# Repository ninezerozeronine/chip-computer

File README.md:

# 16 bit Computer

This is a project to make a basic but fully functional 16 bit computer 
using 7400 series ICs.

The full docs can be found on the Read the Docs: https://eight-bit-computer.readthedocs.io/

# Docs

To build the docs on mac run:

    make clean
    make html

in `docs`.

To build the docs in windows run:

    sphinx-build.exe . _build

in `docs`. This also runs the apidoc command on build with a convenience function in conf.py.

# Tests

To run the tests, run:

    tox

in the root directory. Note that in pytest.ini the tests directory is specified as the test directory.

Run:

    tox -e test -- -m "not slow"

To avoid the slow checks.

To generate a coverage report run:

    tox -e cov

in the root directory.

# Development

This is assuming the OS is Windows and Anaconda is being used for Python/Environment managemnet.

If one hasn't already been created, create a virtualenv with:

    conda create --name chipcomputerenv python=3.11

Then activate the virtualenv:

    conda activate sbcdevenv

Then install the package into the dev env by running the following in the root directory:

    python -m pip install .

# Release

    python setup.py sdist bdist_wheel
    python -m twine upload dist/*

# License

The content of this project itself is licensed under the
[Attribution-ShareAlike 4.0 International
license](http://creativecommons.org/licenses/by-sa/4.0/), and any source code used
in conjunction with the project is licensed under the [MIT
license](http://opensource.org/licenses/mit-license.php).

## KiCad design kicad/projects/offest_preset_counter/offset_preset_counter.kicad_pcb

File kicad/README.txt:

templates
    KiCad templates for boards in the computer
    https://docs.kicad-pcb.org/5.1/en/kicad/kicad.html#project_templates

symbol_libs
    Symbol libraries shared between the KiCad project.
    The templates are set up to point to these.

projects
    A folder to contain the KiCad projects.
    Each board is it's own project.

footprint_libs
    Footprint libraries shared between the KiCad projects.
    The templates are set up to point to these.

Library referncing is achieved via the KiCad variable replacement in the project library settings:
    ${KIPRJMOD}\..\..\symbol_libs\eight-bit-computer.lib
    ${KIPRJMOD}\..\..\footprint_libs\eight-bit-computer.pretty

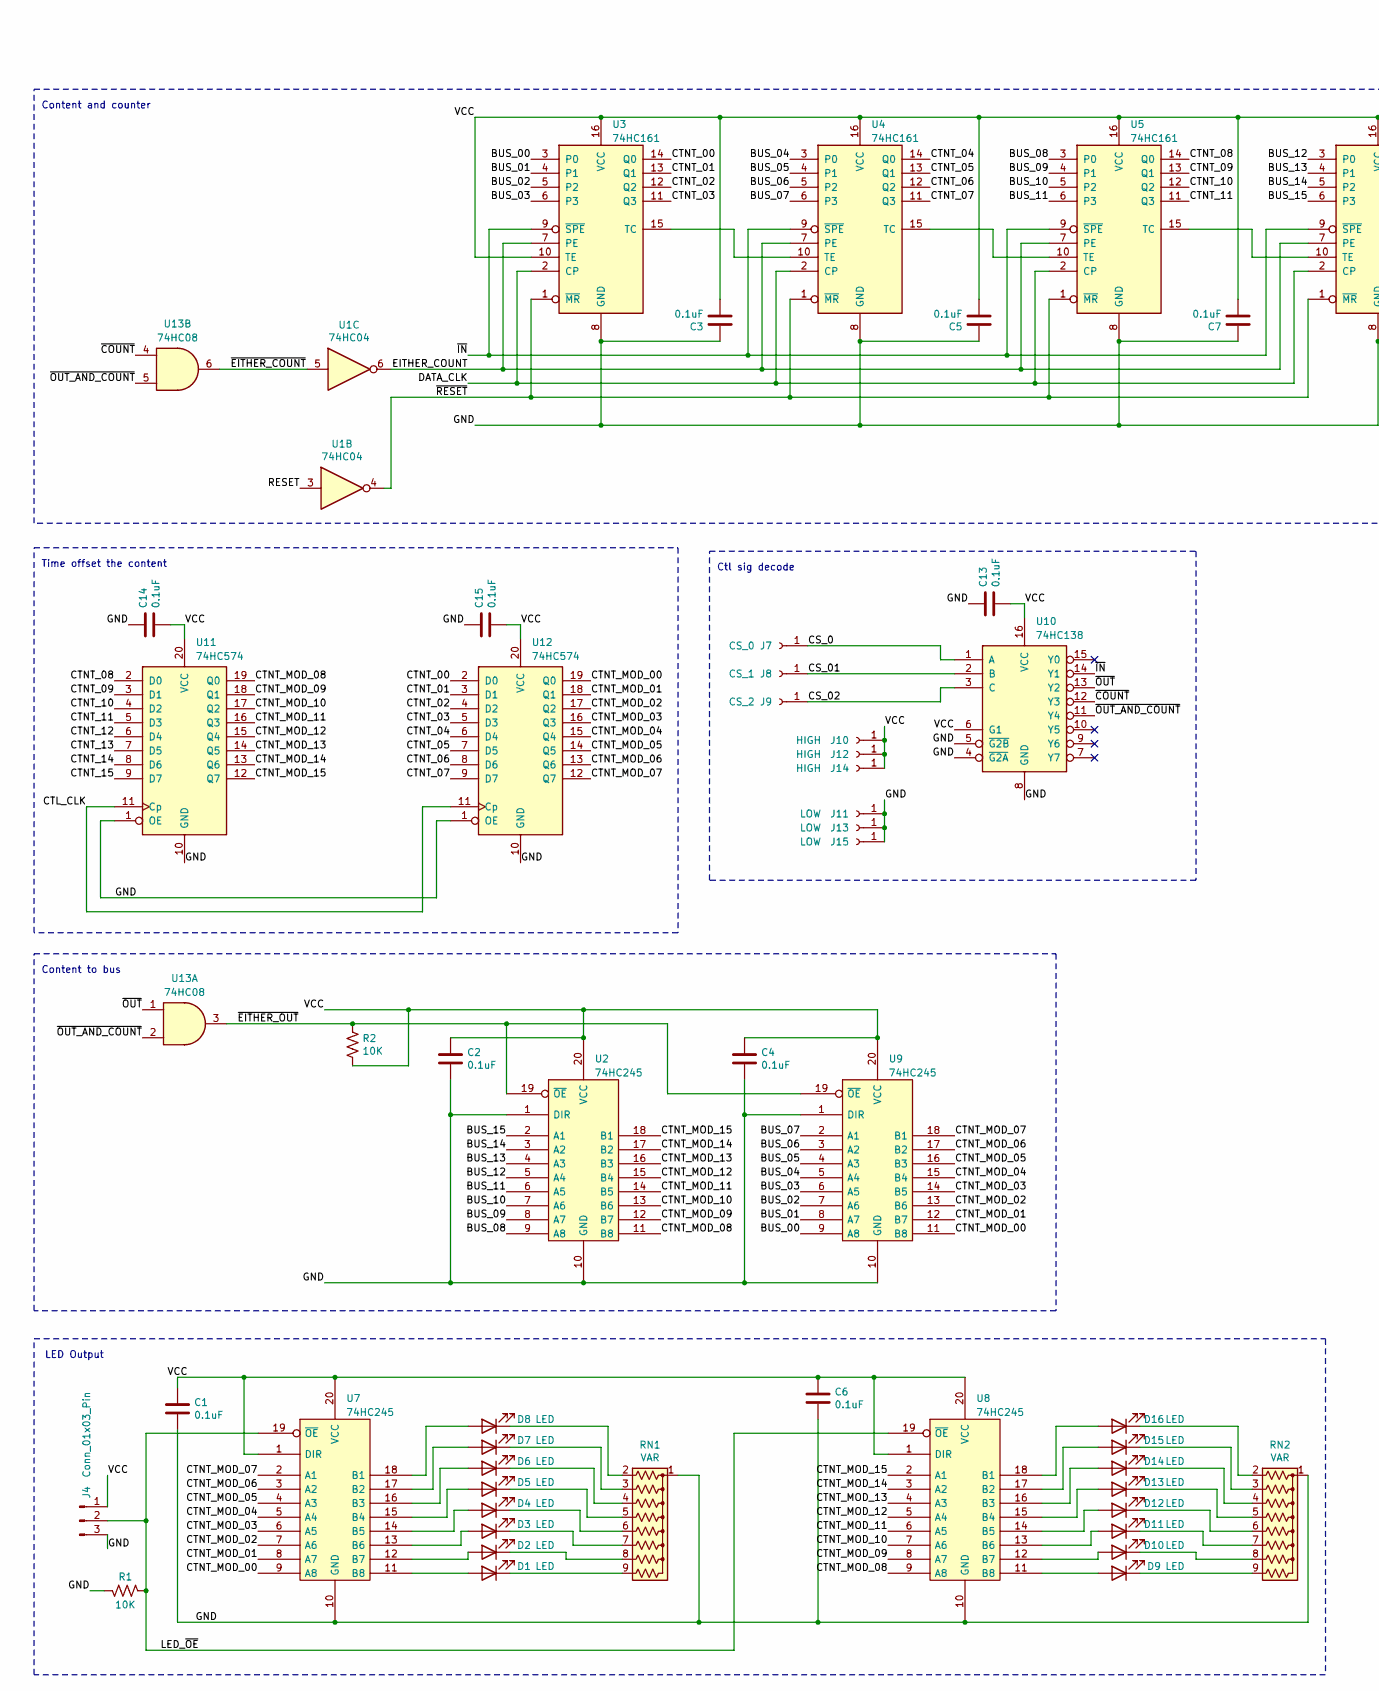
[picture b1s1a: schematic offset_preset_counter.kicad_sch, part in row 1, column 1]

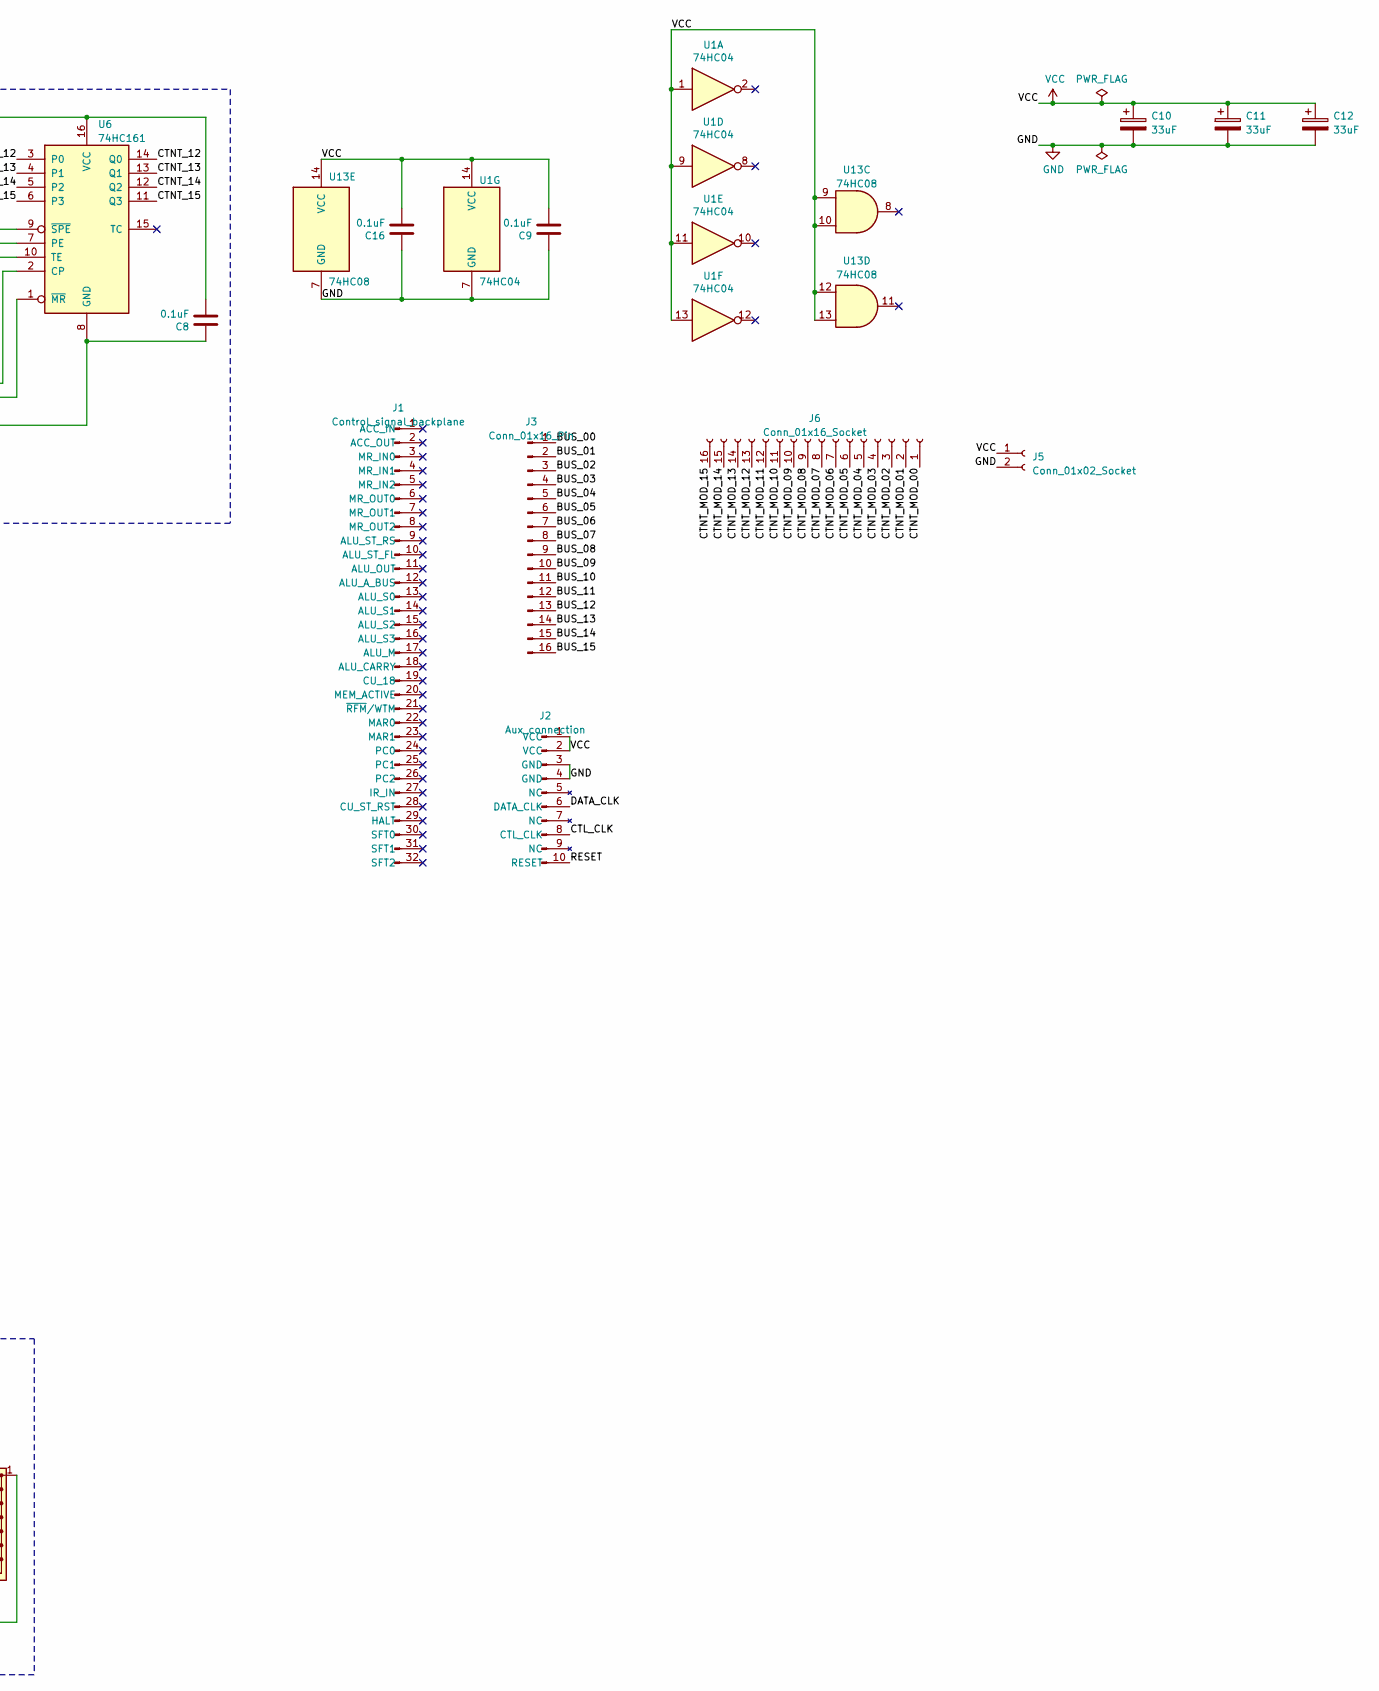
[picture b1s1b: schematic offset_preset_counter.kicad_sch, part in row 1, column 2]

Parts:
C1, C2, C3, C4, C5, C6, C7, C8, C9, C13, C14, C15, C16: 0.1uF; C_Disc_D5.0mm_W2.5mm_P5.00mm
C10, C11, C12: 33uF; CP_Radial_D6.3mm_P2.50mm
D1, D2, D3, D4, D5, D6, D7, D8, D9, D10, D11, D12, D13, D14, D15, D16: LED; LED_D5.0mm_Horizontal_O3.81mm_Z3.0mm
J1: Control_signal_backplane; backplane-connector-annotated
J2: Aux_connection; aux-connection
J3: Conn_01x16_Pin; bus-connection
J4: Conn_01x03_Pin; PinHeader_1x03_P2.54mm_Horizontal
J5: Conn_01x02_Socket; PinSocket_1x02_P2.54mm_Horizontal
J6: Conn_01x16_Socket; PinSocket_1x16_P2.54mm_Horizontal
J7: CS_0; SolderWire-0.5sqmm_1x01_D0.9mm_OD2.3mm
J8: CS_1; SolderWire-0.5sqmm_1x01_D0.9mm_OD2.3mm
J9: CS_2; SolderWire-0.5sqmm_1x01_D0.9mm_OD2.3mm
J10, J12, J14: HIGH; SolderWire-0.5sqmm_1x01_D0.9mm_OD2.3mm
J11, J13, J15: LOW; SolderWire-0.5sqmm_1x01_D0.9mm_OD2.3mm
R1, R2: 10K; R_Axial_DIN0207_L6.3mm_D2.5mm_P10.16mm_Horizontal
RN1, RN2: VAR; R_Array_SIP9
U1: 74HC04; DIP-14_W7.62mm_Socket
U2, U7, U8, U9: 74HC245; DIP-20_W7.62mm_Socket
U3, U4, U5, U6: 74HC161; DIP-16_W7.62mm_Socket
U10: 74HC138; DIP-16_W7.62mm_Socket
U11, U12: 74HC574; DIP-20_W7.62mm_Socket
U13: 74HC08; DIP-14_W7.62mm_Socket

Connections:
/BUS_00: J3.1, U3.3 (P0), U9.9 (A8)
/BUS_01: J3.2, U3.4 (P1), U9.8 (A7)
/BUS_02: J3.3, U3.5 (P2), U9.7 (A6)
/BUS_03: J3.4, U3.6 (P3), U9.6 (A5)
/BUS_04: J3.5, U4.3 (P0), U9.5 (A4)
/BUS_05: J3.6, U4.4 (P1), U9.4 (A3)
/BUS_06: J3.7, U4.5 (P2), U9.3 (A2)
/BUS_07: J3.8, U4.6 (P3), U9.2 (A1)
/BUS_08: J3.9, U2.9 (A8), U5.3 (P0)
/BUS_09: J3.10, U2.8 (A7), U5.4 (P1)
/BUS_10: J3.11, U2.7 (A6), U5.5 (P2)
/BUS_11: J3.12, U2.6 (A5), U5.6 (P3)
/BUS_12: J3.13, U2.5 (A4), U6.3 (P0)
/BUS_13: J3.14, U2.4 (A3), U6.4 (P1)
/BUS_14: J3.15, U2.3 (A2), U6.5 (P2)
/BUS_15: J3.16, U2.2 (A1), U6.6 (P3)
/CS_0: J7.1, U10.1 (A)
/CS_01: J8.1, U10.2 (B)
/CS_02: J9.1, U10.3 (C)
/CTL_CLK: J2.8 (CTL_CLK), U11.11 (Cp), U12.11 (Cp)
/CTNT_00: U3.14 (Q0), U12.2 (D0)
/CTNT_01: U3.13 (Q1), U12.3 (D1)
/CTNT_02: U3.12 (Q2), U12.4 (D2)
/CTNT_03: U3.11 (Q3), U12.5 (D3)
/CTNT_04: U4.14 (Q0), U12.6 (D4)
/CTNT_05: U4.13 (Q1), U12.7 (D5)
/CTNT_06: U4.12 (Q2), U12.8 (D6)
/CTNT_07: U4.11 (Q3), U12.9 (D7)
/CTNT_08: U5.14 (Q0), U11.2 (D0)
/CTNT_09: U5.13 (Q1), U11.3 (D1)
/CTNT_10: U5.12 (Q2), U11.4 (D2)
/CTNT_11: U5.11 (Q3), U11.5 (D3)
/CTNT_12: U6.14 (Q0), U11.6 (D4)
/CTNT_13: U6.13 (Q1), U11.7 (D5)
/CTNT_14: U6.12 (Q2), U11.8 (D6)
/CTNT_15: U6.11 (Q3), U11.9 (D7)
/CTNT_MOD_00: J6.1, U7.9 (A8), U9.11 (B8), U12.19 (Q0)
/CTNT_MOD_01: J6.2, U7.8 (A7), U9.12 (B7), U12.18 (Q1)
/CTNT_MOD_02: J6.3, U7.7 (A6), U9.13 (B6), U12.17 (Q2)
/CTNT_MOD_03: J6.4, U7.6 (A5), U9.14 (B5), U12.16 (Q3)
/CTNT_MOD_04: J6.5, U7.5 (A4), U9.15 (B4), U12.15 (Q4)
/CTNT_MOD_05: J6.6, U7.4 (A3), U9.16 (B3), U12.14 (Q5)
/CTNT_MOD_06: J6.7, U7.3 (A2), U9.17 (B2), U12.13 (Q6)
/CTNT_MOD_07: J6.8, U7.2 (A1), U9.18 (B1), U12.12 (Q7)
/CTNT_MOD_08: J6.9, U2.11 (B8), U8.9 (A8), U11.19 (Q0)
/CTNT_MOD_09: J6.10, U2.12 (B7), U8.8 (A7), U11.18 (Q1)
/CTNT_MOD_10: J6.11, U2.13 (B6), U8.7 (A6), U11.17 (Q2)
/CTNT_MOD_11: J6.12, U2.14 (B5), U8.6 (A5), U11.16 (Q3)
/CTNT_MOD_12: J6.13, U2.15 (B4), U8.5 (A4), U11.15 (Q4)
/CTNT_MOD_13: J6.14, U2.16 (B3), U8.4 (A3), U11.14 (Q5)
/CTNT_MOD_14: J6.15, U2.17 (B2), U8.3 (A2), U11.13 (Q6)
/CTNT_MOD_15: J6.16, U2.18 (B1), U8.2 (A1), U11.12 (Q7)
/DATA_CLK: J2.6 (DATA_CLK), U3.2 (CP), U4.2 (CP), U5.2 (CP), U6.2 (CP)
/EITHER_COUNT: U1.6, U3.7 (PE), U4.7 (PE), U5.7 (PE), U6.7 (PE)
/LED_~OE: J4.2, R1.1, U7.19 (~OE), U8.19 (~OE)
/RESET: J2.10 (RESET), U1.3
/~COUNT: U10.12 (Y3), U13.4
/~EITHER_COUNT: U1.5, U13.6
/~EITHER_OUT: R2.1, U2.19 (~OE), U9.19 (~OE), U13.3
/~IN: U3.9 (~SPE), U4.9 (~SPE), U5.9 (~SPE), U6.9 (~SPE), U10.14 (Y1)
/~OUT_AND_COUNT: U10.11 (Y4), U13.2, U13.5
/~OUT: U10.13 (Y2), U13.1
/~RESET: U1.4, U3.1 (~MR), U4.1 (~MR), U5.1 (~MR), U6.1 (~MR)
GND: C1.2, C2.2, C3.1, C4.2, C5.1, C6.2, C7.1, C8.1, C9.1, C10.2, C11.2, C12.2, C13.1, C14.1, C15.1, C16.1, J2.3 (GND), J2.4 (GND), J4.3, J5.2, J11.1, J13.1, J15.1, R1.2, RN1.1 (common), RN2.1 (common), U1.7 (GND), U2.1 (DIR), U2.10 (GND), U3.8 (GND), U4.8 (GND), U5.8 (GND), U6.8 (GND), U7.10 (GND), U8.10 (GND), U9.1 (DIR), U9.10 (GND), U10.4 (~G2A), U10.5 (~G2B), U10.8 (GND), U11.1 (OE), U11.10 (GND), U12.1 (OE), U12.10 (GND), U13.7 (GND)
unnamed: D1.2 (A), U7.11 (B8)
unnamed: D1.1 (K), RN1.9 (R8)
unnamed: D2.2 (A), U7.12 (B7)
unnamed: D2.1 (K), RN1.8 (R7)
unnamed: D3.2 (A), U7.13 (B6)
unnamed: D3.1 (K), RN1.7 (R6)
unnamed: D4.2 (A), U7.14 (B5)
unnamed: D4.1 (K), RN1.6 (R5)
unnamed: D5.2 (A), U7.15 (B4)
unnamed: D5.1 (K), RN1.5 (R4)
unnamed: D6.2 (A), U7.16 (B3)
unnamed: D6.1 (K), RN1.4 (R3)
unnamed: D7.2 (A), U7.17 (B2)
unnamed: D7.1 (K), RN1.3 (R2)
unnamed: D8.2 (A), U7.18 (B1)
unnamed: D8.1 (K), RN1.2 (R1)
unnamed: D9.2 (A), U8.11 (B8)
unnamed: D9.1 (K), RN2.9 (R8)
unnamed: D10.2 (A), U8.12 (B7)
unnamed: D10.1 (K), RN2.8 (R7)
unnamed: D11.2 (A), U8.13 (B6)
unnamed: D11.1 (K), RN2.7 (R6)
unnamed: D12.2 (A), U8.14 (B5)
unnamed: D12.1 (K), RN2.6 (R5)
unnamed: D13.2 (A), U8.15 (B4)
unnamed: D13.1 (K), RN2.5 (R4)
unnamed: D14.2 (A), U8.16 (B3)
unnamed: D14.1 (K), RN2.4 (R3)
unnamed: D15.2 (A), U8.17 (B2)
unnamed: D15.1 (K), RN2.3 (R2)
unnamed: D16.2 (A), U8.18 (B1)
unnamed: D16.1 (K), RN2.2 (R1)
unnamed: U3.15 (TC), U4.10 (TE)
unnamed: U4.15 (TC), U5.10 (TE)
unnamed: U5.15 (TC), U6.10 (TE)
VCC: C1.1, C2.1, C3.2, C4.1, C5.2, C6.1, C7.2, C8.2, C9.2, C10.1, C11.1, C12.1, C13.2, C14.2, C15.2, C16.2, J2.1 (VCC), J2.2 (VCC), J4.1, J5.1, J10.1, J12.1, J14.1, R2.2, U1.1, U1.9, U1.11, U1.13, U1.14 (VCC), U2.20 (VCC), U3.10 (TE), U3.16 (VCC), U4.16 (VCC), U5.16 (VCC), U6.16 (VCC), U7.1 (DIR), U7.20 (VCC), U8.1 (DIR), U8.20 (VCC), U9.20 (VCC), U10.6 (G1), U10.16 (VCC), U11.20 (VCC), U12.20 (VCC), U13.9, U13.10, U13.12, U13.13, U13.14 (VCC)

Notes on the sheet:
LED Output
Time offset the content
Content and counter
Ctl sig decode
Content to bus

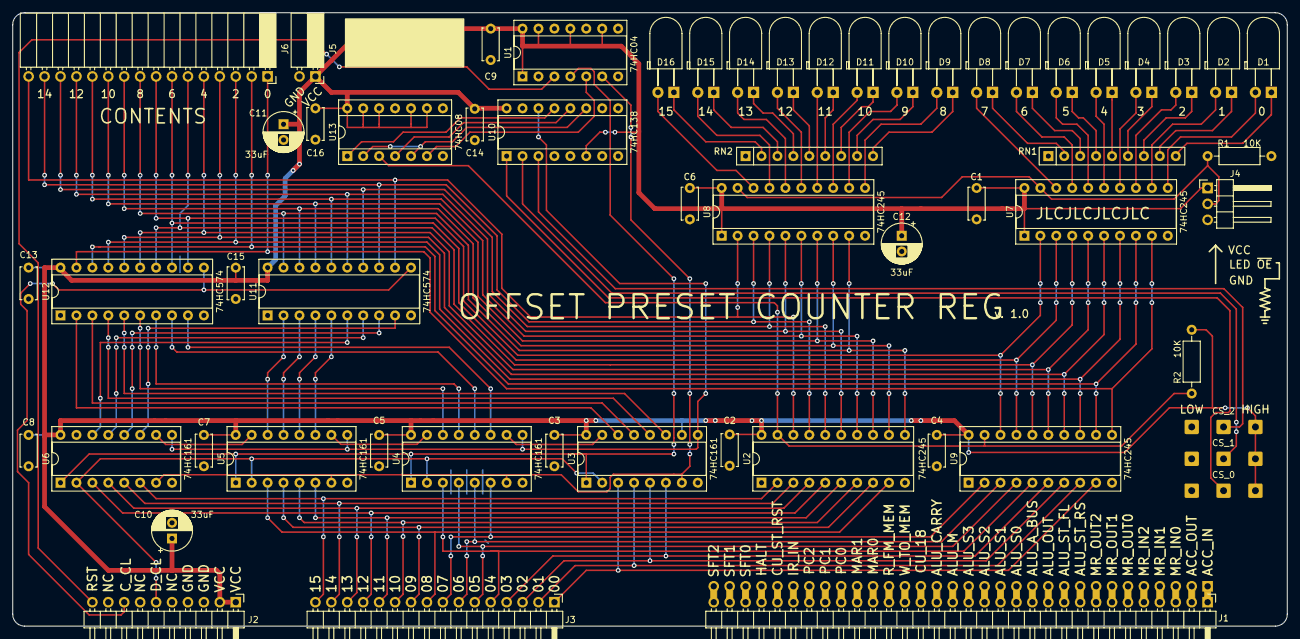
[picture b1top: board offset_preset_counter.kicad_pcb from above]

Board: 2 copper layers, 203.2 x 97.8 mm, 64 parts (0 on the bottom side), 100 nets.

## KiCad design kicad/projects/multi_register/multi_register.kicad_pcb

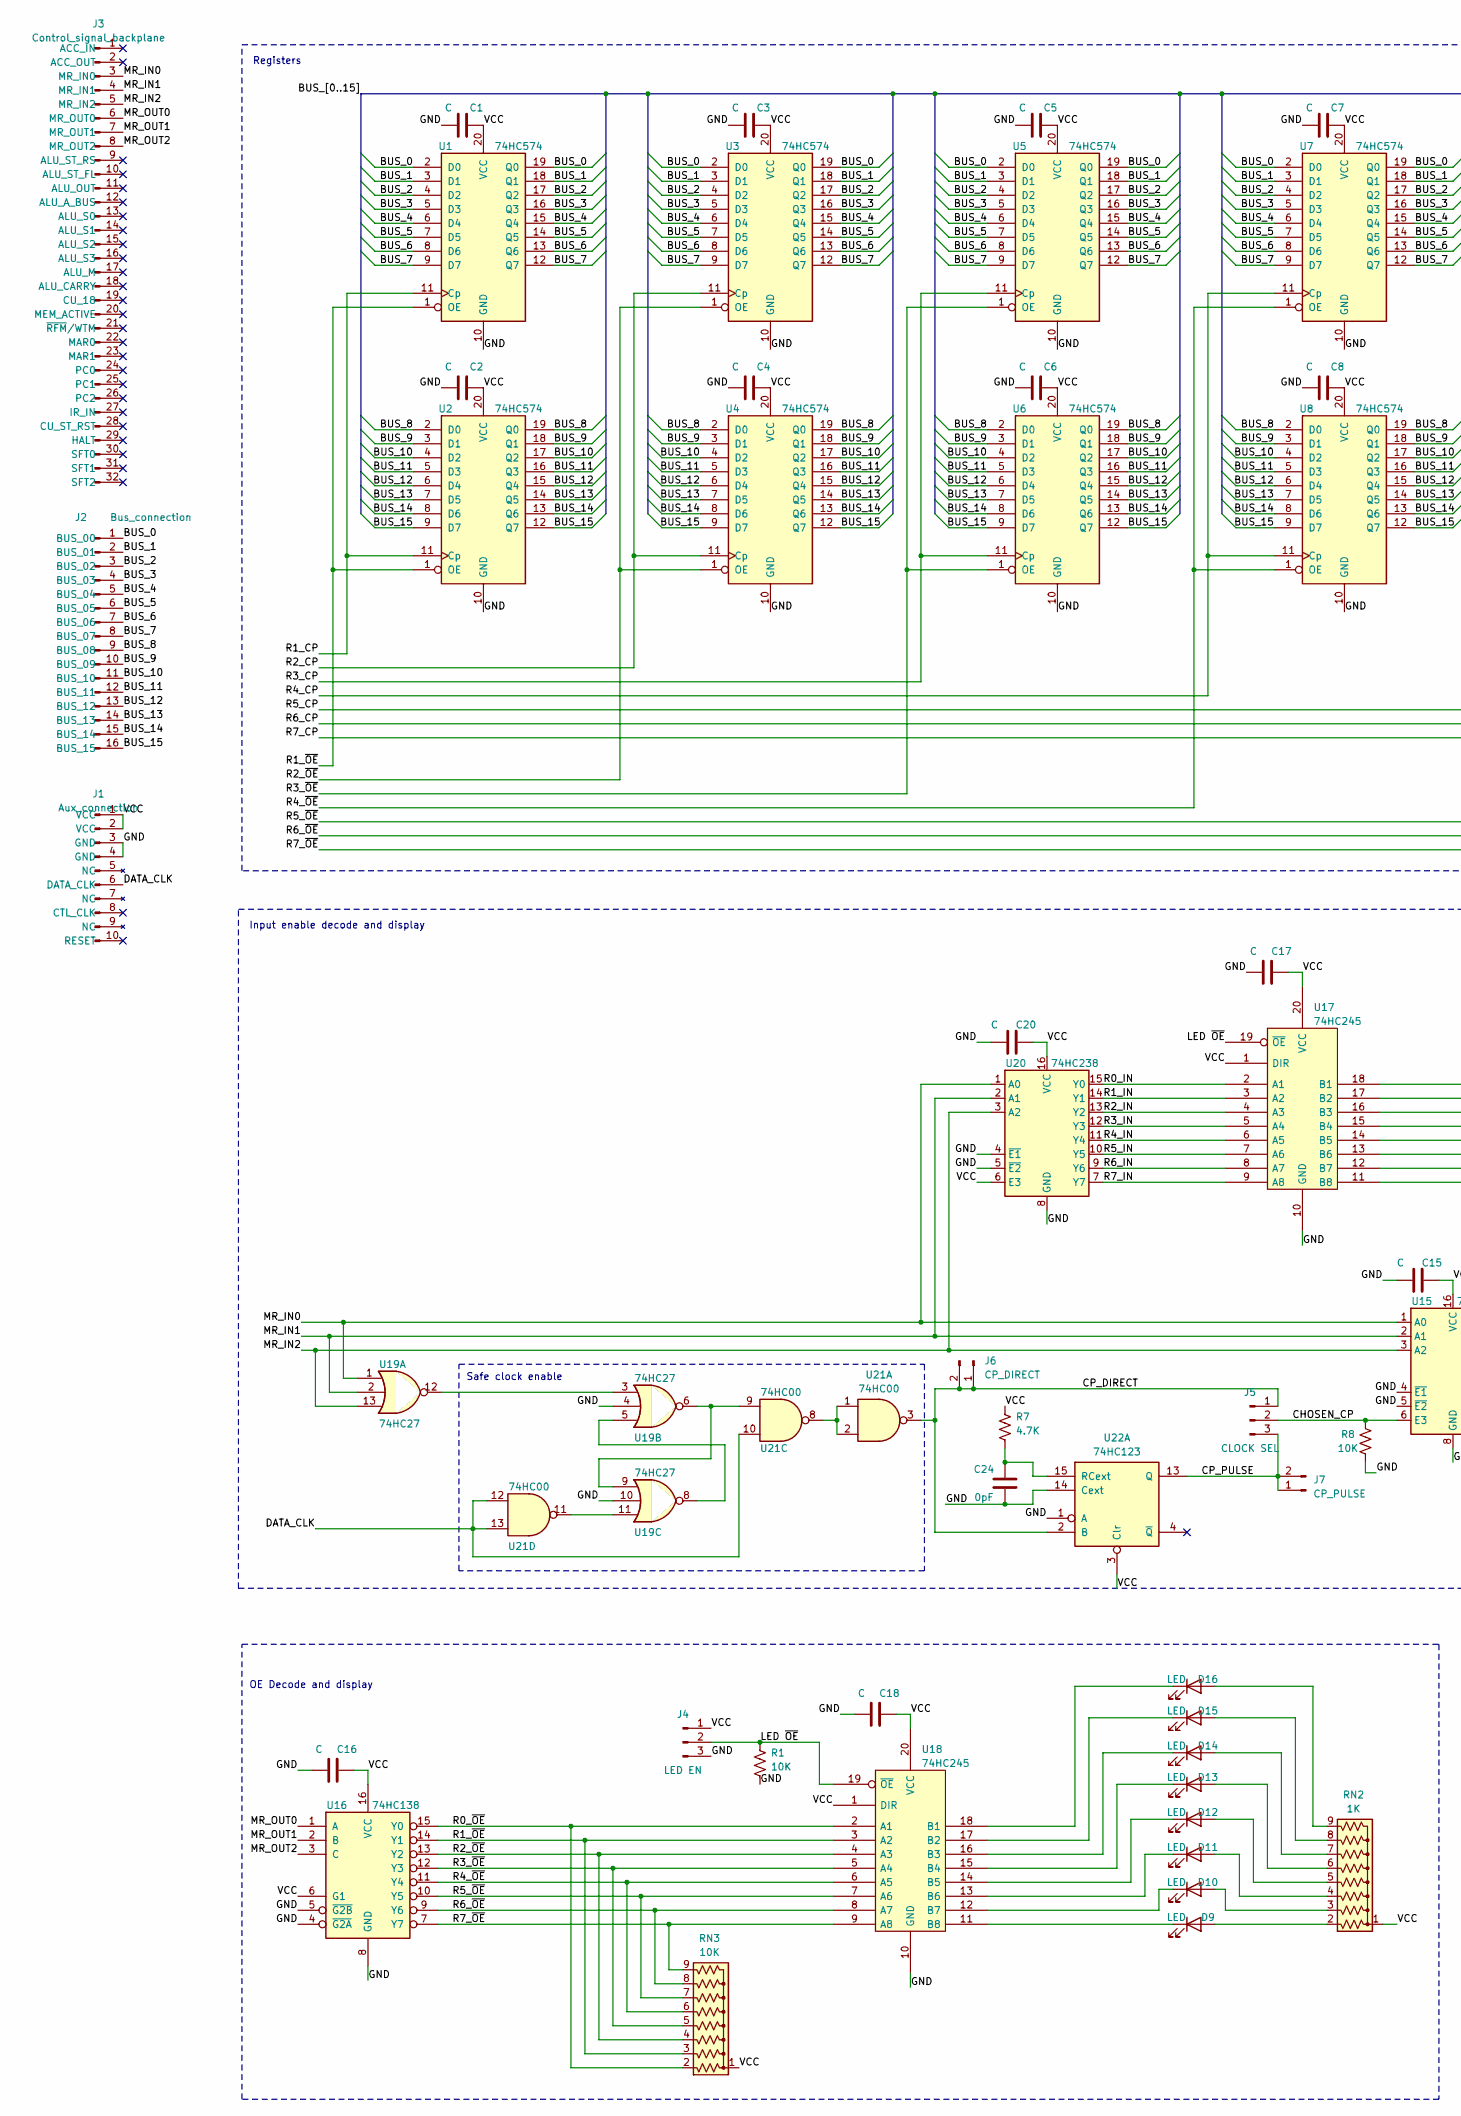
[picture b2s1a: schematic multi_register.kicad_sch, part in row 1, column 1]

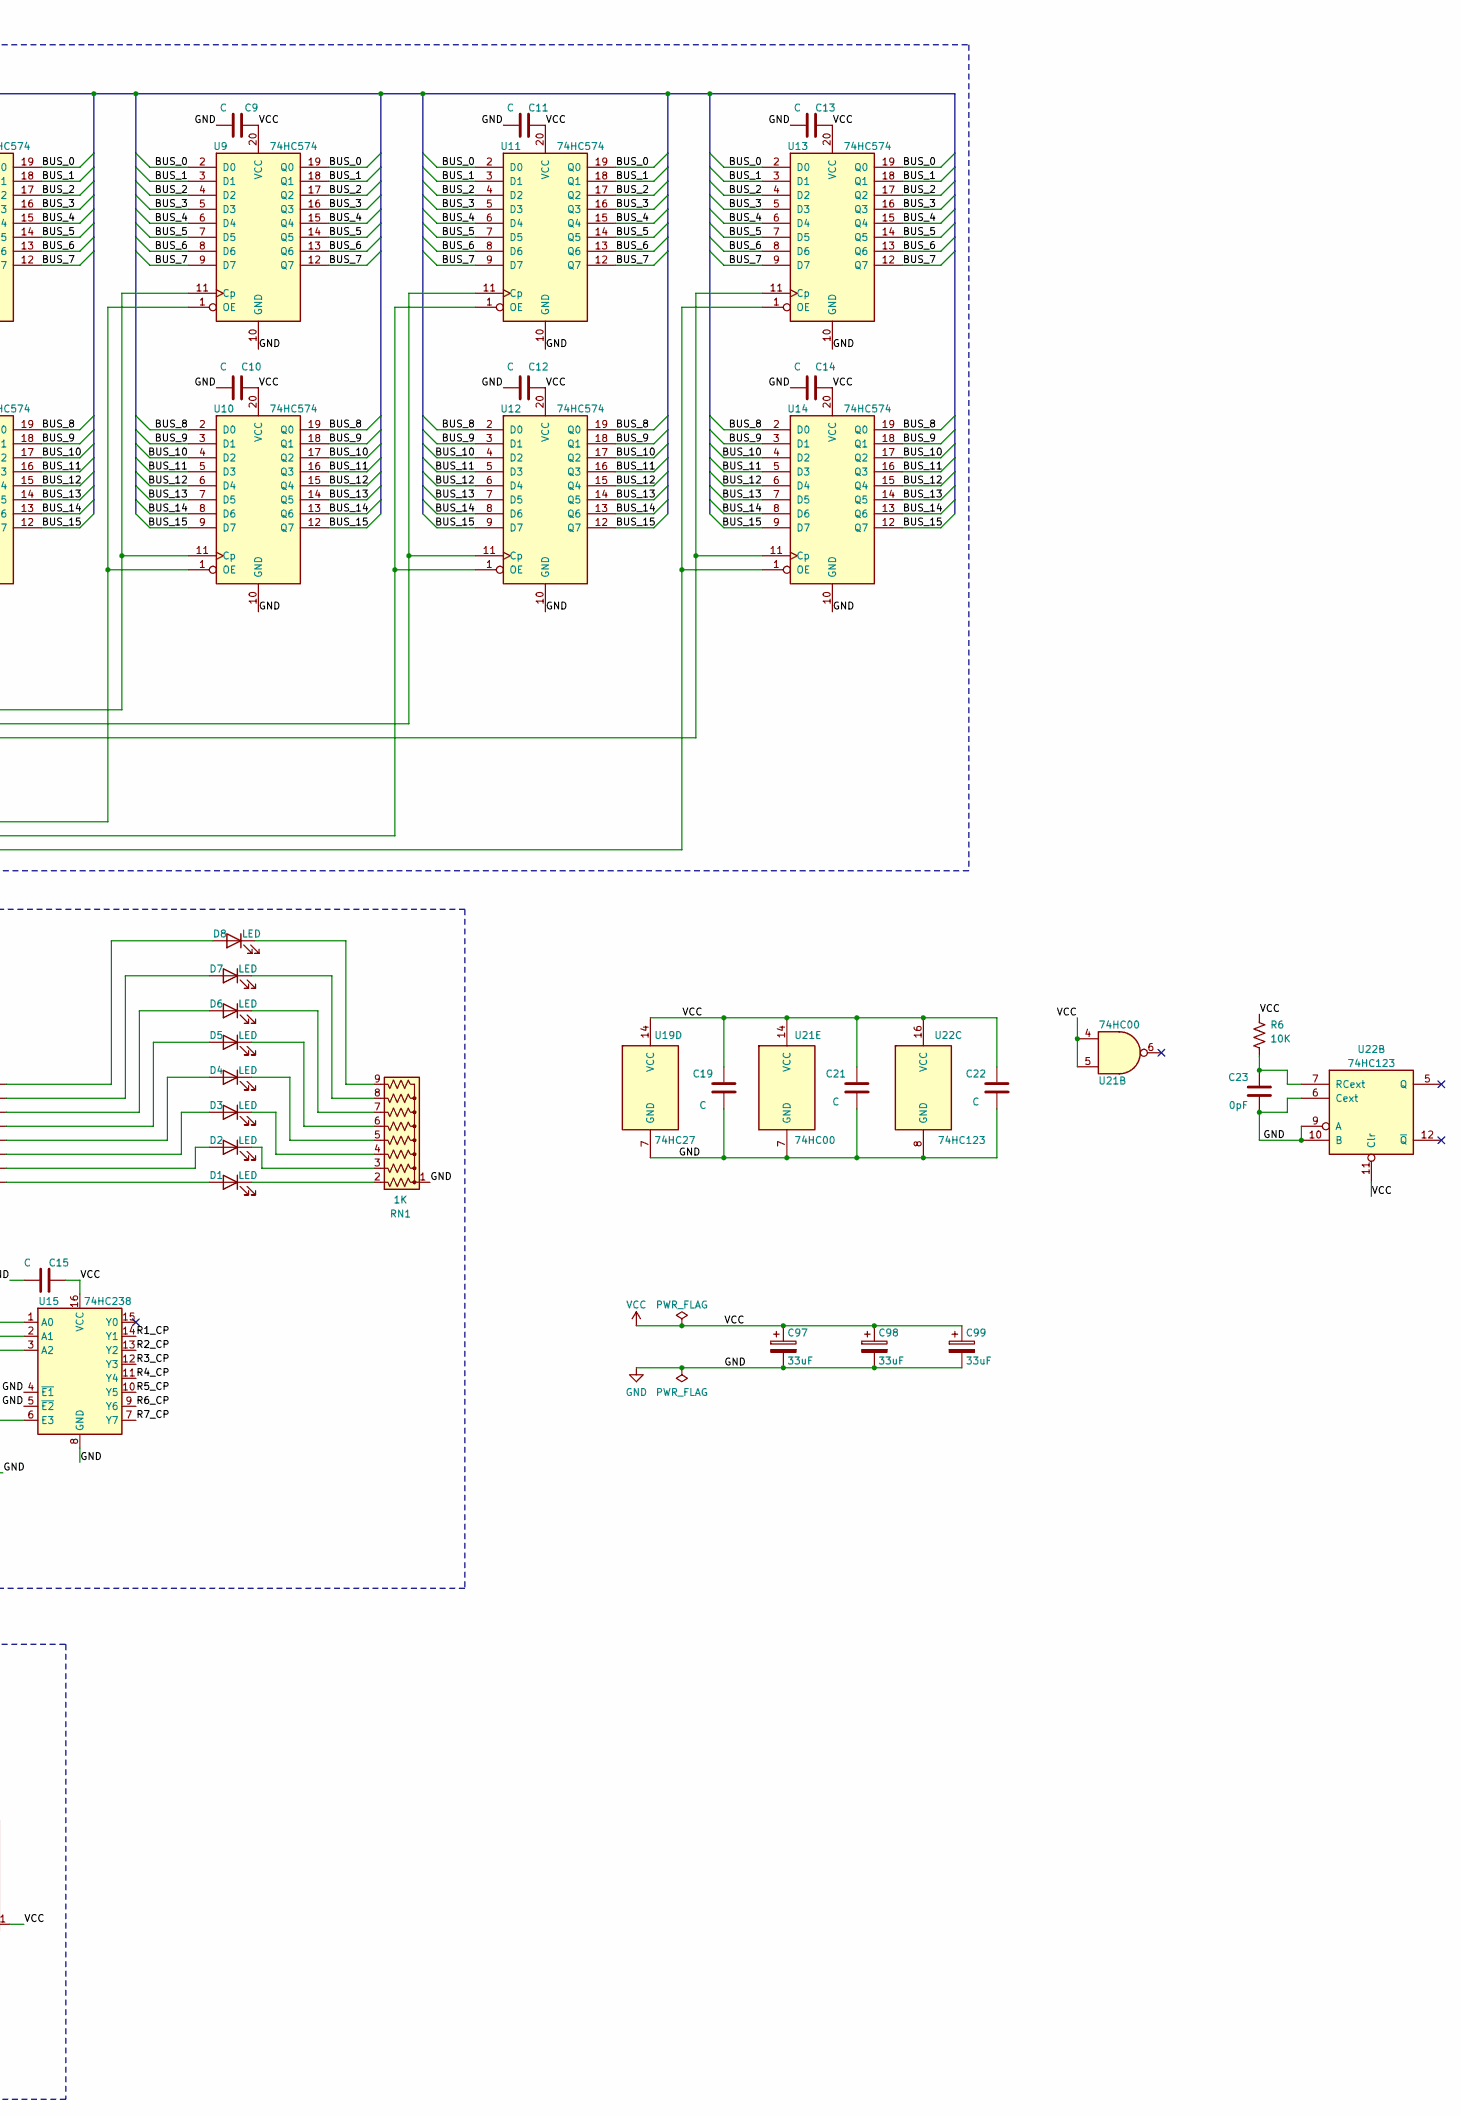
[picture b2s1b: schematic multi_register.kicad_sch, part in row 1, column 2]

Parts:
C1, C2, C3, C4, C5, C6, C7, C8, C9, C10, C11, C12, C13, C14, C15, C16, C17, C18, C19, C20, C21, C22: C; C_Disc_D5.0mm_W2.5mm_P5.00mm
C23, C24: 0pF; C_Disc_D5.0mm_W2.5mm_P5.00mm
C97, C98, C99: 33uF; CP_Radial_D6.3mm_P2.50mm
D1, D2, D3, D4, D5, D6, D7, D8, D9, D10, D11, D12, D13, D14, D15, D16: LED; LED_D5.0mm_Horizontal_O3.81mm_Z3.0mm
J1: Aux_connection; aux-connection
J2: Bus_connection; bus-connection
J3: Control_signal_backplane; backplane-connector-single-row-annotated
J4: LED EN; PinHeader_1x03_P2.54mm_Horizontal
J5: CLOCK SEL; PinHeader_1x03_P2.54mm_Horizontal
J6: CP_DIRECT; PinHeader_1x02_P2.54mm_Vertical
J7: CP_PULSE; PinHeader_1x02_P2.54mm_Vertical
R1, R6, R8: 10K; R_Axial_DIN0207_L6.3mm_D2.5mm_P10.16mm_Horizontal
R7: 4.7K; R_Axial_DIN0207_L6.3mm_D2.5mm_P10.16mm_Horizontal
RN1, RN2: 1K; R_Array_SIP9
RN3: 10K; R_Array_SIP9
U1, U2, U3, U4, U5, U6, U7, U8, U9, U10, U11, U12, U13, U14: 74HC574; DIP-20_W7.62mm_Socket
U15, U20: 74HC238; DIP-16_W7.62mm_Socket
U16: 74HC138; DIP-16_W7.62mm_Socket
U17, U18: 74HC245; DIP-20_W7.62mm_Socket
U19: 74HC27; DIP-14_W7.62mm_Socket
U21: 74HC00; DIP-14_W7.62mm_Socket
U22: 74HC123; DIP-16_W7.62mm_Socket

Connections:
/BUS_0: J2.1 (BUS_00), U1.2 (D0), U1.19 (Q0), U3.2 (D0), U3.19 (Q0), U5.2 (D0), U5.19 (Q0), U7.2 (D0), U7.19 (Q0), U9.2 (D0), U9.19 (Q0), U11.2 (D0), U11.19 (Q0), U13.2 (D0), U13.19 (Q0)
/BUS_1: J2.2 (BUS_01), U1.3 (D1), U1.18 (Q1), U3.3 (D1), U3.18 (Q1), U5.3 (D1), U5.18 (Q1), U7.3 (D1), U7.18 (Q1), U9.3 (D1), U9.18 (Q1), U11.3 (D1), U11.18 (Q1), U13.3 (D1), U13.18 (Q1)
/BUS_2: J2.3 (BUS_02), U1.4 (D2), U1.17 (Q2), U3.4 (D2), U3.17 (Q2), U5.4 (D2), U5.17 (Q2), U7.4 (D2), U7.17 (Q2), U9.4 (D2), U9.17 (Q2), U11.4 (D2), U11.17 (Q2), U13.4 (D2), U13.17 (Q2)
/BUS_3: J2.4 (BUS_03), U1.5 (D3), U1.16 (Q3), U3.5 (D3), U3.16 (Q3), U5.5 (D3), U5.16 (Q3), U7.5 (D3), U7.16 (Q3), U9.5 (D3), U9.16 (Q3), U11.5 (D3), U11.16 (Q3), U13.5 (D3), U13.16 (Q3)
/BUS_4: J2.5 (BUS_04), U1.6 (D4), U1.15 (Q4), U3.6 (D4), U3.15 (Q4), U5.6 (D4), U5.15 (Q4), U7.6 (D4), U7.15 (Q4), U9.6 (D4), U9.15 (Q4), U11.6 (D4), U11.15 (Q4), U13.6 (D4), U13.15 (Q4)
/BUS_5: J2.6 (BUS_05), U1.7 (D5), U1.14 (Q5), U3.7 (D5), U3.14 (Q5), U5.7 (D5), U5.14 (Q5), U7.7 (D5), U7.14 (Q5), U9.7 (D5), U9.14 (Q5), U11.7 (D5), U11.14 (Q5), U13.7 (D5), U13.14 (Q5)
/BUS_6: J2.7 (BUS_06), U1.8 (D6), U1.13 (Q6), U3.8 (D6), U3.13 (Q6), U5.8 (D6), U5.13 (Q6), U7.8 (D6), U7.13 (Q6), U9.8 (D6), U9.13 (Q6), U11.8 (D6), U11.13 (Q6), U13.8 (D6), U13.13 (Q6)
/BUS_7: J2.8 (BUS_07), U1.9 (D7), U1.12 (Q7), U3.9 (D7), U3.12 (Q7), U5.9 (D7), U5.12 (Q7), U7.9 (D7), U7.12 (Q7), U9.9 (D7), U9.12 (Q7), U11.9 (D7), U11.12 (Q7), U13.9 (D7), U13.12 (Q7)
/BUS_8: J2.9 (BUS_08), U2.2 (D0), U2.19 (Q0), U4.2 (D0), U4.19 (Q0), U6.2 (D0), U6.19 (Q0), U8.2 (D0), U8.19 (Q0), U10.2 (D0), U10.19 (Q0), U12.2 (D0), U12.19 (Q0), U14.2 (D0), U14.19 (Q0)
/BUS_9: J2.10 (BUS_09), U2.3 (D1), U2.18 (Q1), U4.3 (D1), U4.18 (Q1), U6.3 (D1), U6.18 (Q1), U8.3 (D1), U8.18 (Q1), U10.3 (D1), U10.18 (Q1), U12.3 (D1), U12.18 (Q1), U14.3 (D1), U14.18 (Q1)
/BUS_10: J2.11 (BUS_10), U2.4 (D2), U2.17 (Q2), U4.4 (D2), U4.17 (Q2), U6.4 (D2), U6.17 (Q2), U8.4 (D2), U8.17 (Q2), U10.4 (D2), U10.17 (Q2), U12.4 (D2), U12.17 (Q2), U14.4 (D2), U14.17 (Q2)
/BUS_11: J2.12 (BUS_11), U2.5 (D3), U2.16 (Q3), U4.5 (D3), U4.16 (Q3), U6.5 (D3), U6.16 (Q3), U8.5 (D3), U8.16 (Q3), U10.5 (D3), U10.16 (Q3), U12.5 (D3), U12.16 (Q3), U14.5 (D3), U14.16 (Q3)
/BUS_12: J2.13 (BUS_12), U2.6 (D4), U2.15 (Q4), U4.6 (D4), U4.15 (Q4), U6.6 (D4), U6.15 (Q4), U8.6 (D4), U8.15 (Q4), U10.6 (D4), U10.15 (Q4), U12.6 (D4), U12.15 (Q4), U14.6 (D4), U14.15 (Q4)
/BUS_13: J2.14 (BUS_13), U2.7 (D5), U2.14 (Q5), U4.7 (D5), U4.14 (Q5), U6.7 (D5), U6.14 (Q5), U8.7 (D5), U8.14 (Q5), U10.7 (D5), U10.14 (Q5), U12.7 (D5), U12.14 (Q5), U14.7 (D5), U14.14 (Q5)
/BUS_14: J2.15 (BUS_14), U2.8 (D6), U2.13 (Q6), U4.8 (D6), U4.13 (Q6), U6.8 (D6), U6.13 (Q6), U8.8 (D6), U8.13 (Q6), U10.8 (D6), U10.13 (Q6), U12.8 (D6), U12.13 (Q6), U14.8 (D6), U14.13 (Q6)
/BUS_15: J2.16 (BUS_15), U2.9 (D7), U2.12 (Q7), U4.9 (D7), U4.12 (Q7), U6.9 (D7), U6.12 (Q7), U8.9 (D7), U8.12 (Q7), U10.9 (D7), U10.12 (Q7), U12.9 (D7), U12.12 (Q7), U14.9 (D7), U14.12 (Q7)
/CHOSEN_CP: J5.2, R8.2, U15.6 (E3)
/CP_DIRECT: J5.1, J6.1, J6.2, U21.3, U22.2 (B)
/CP_PULSE: J5.3, J7.1, J7.2, U22.13 (Q)
/DATA_CLK: J1.6 (DATA_CLK), U21.10, U21.12, U21.13
/LED ~OE: J4.2, R1.1, U17.19 (~OE), U18.19 (~OE)
/MR_IN0: J3.3 (MR_IN0), U15.1 (A0), U19.1, U20.1 (A0)
/MR_IN1: J3.4 (MR_IN1), U15.2 (A1), U19.2, U20.2 (A1)
/MR_IN2: J3.5 (MR_IN2), U15.3 (A2), U19.13, U20.3 (A2)
/MR_OUT0: J3.6 (MR_OUT0), U16.1 (A)
/MR_OUT1: J3.7 (MR_OUT1), U16.2 (B)
/MR_OUT2: J3.8 (MR_OUT2), U16.3 (C)
/R0_IN: U17.2 (A1), U20.15 (Y0)
/R0_~OE: RN3.2 (R1), U16.15 (Y0), U18.2 (A1)
/R1_CP: U1.11 (Cp), U2.11 (Cp), U15.14 (Y1)
/R1_IN: U17.3 (A2), U20.14 (Y1)
/R1_~OE: RN3.3 (R2), U1.1 (OE), U2.1 (OE), U16.14 (Y1), U18.3 (A2)
/R2_CP: U3.11 (Cp), U4.11 (Cp), U15.13 (Y2)
/R2_IN: U17.4 (A3), U20.13 (Y2)
/R2_~OE: RN3.4 (R3), U3.1 (OE), U4.1 (OE), U16.13 (Y2), U18.4 (A3)
/R3_CP: U5.11 (Cp), U6.11 (Cp), U15.12 (Y3)
/R3_IN: U17.5 (A4), U20.12 (Y3)
/R3_~OE: RN3.5 (R4), U5.1 (OE), U6.1 (OE), U16.12 (Y3), U18.5 (A4)
/R4_CP: U7.11 (Cp), U8.11 (Cp), U15.11 (Y4)
/R4_IN: U17.6 (A5), U20.11 (Y4)
/R4_~OE: RN3.6 (R5), U7.1 (OE), U8.1 (OE), U16.11 (Y4), U18.6 (A5)
/R5_CP: U9.11 (Cp), U10.11 (Cp), U15.10 (Y5)
/R5_IN: U17.7 (A6), U20.10 (Y5)
/R5_~OE: RN3.7 (R6), U9.1 (OE), U10.1 (OE), U16.10 (Y5), U18.7 (A6)
/R6_CP: U11.11 (Cp), U12.11 (Cp), U15.9 (Y6)
/R6_IN: U17.8 (A7), U20.9 (Y6)
/R6_~OE: RN3.8 (R7), U11.1 (OE), U12.1 (OE), U16.9 (Y6), U18.8 (A7)
/R7_CP: U13.11 (Cp), U14.11 (Cp), U15.7 (Y7)
/R7_IN: U17.9 (A8), U20.7 (Y7)
/R7_~OE: RN3.9 (R8), U13.1 (OE), U14.1 (OE), U16.7 (Y7), U18.9 (A8)
GND: C1.1, C2.1, C3.1, C4.1, C5.1, C6.1, C7.1, C8.1, C9.1, C10.1, C11.1, C12.1, C13.1, C14.1, C15.1, C16.1, C17.1, C18.1, C19.1, C20.1, C21.1, C22.1, C23.1, C24.1, C97.2, C98.2, C99.2, J1.3 (GND), J1.4 (GND), J4.3, R1.2, R8.1, RN1.1 (common), U1.10 (GND), U2.10 (GND), U3.10 (GND), U4.10 (GND), U5.10 (GND), U6.10 (GND), U7.10 (GND), U8.10 (GND), U9.10 (GND), U10.10 (GND), U11.10 (GND), U12.10 (GND), U13.10 (GND), U14.10 (GND), U15.4 (~E1), U15.5 (~E2), U15.8 (GND), U16.4 (~G2A), U16.5 (~G2B), U16.8 (GND), U17.10 (GND), U18.10 (GND), U19.4, U19.7 (GND), U19.10, U20.4 (~E1), U20.5 (~E2), U20.8 (GND), U21.7 (GND), U22.1 (A), U22.6 (Cext), U22.8 (GND), U22.9 (A), U22.10 (B), U22.14 (Cext)
unnamed: D1.2 (A), U17.11 (B8)
unnamed: D1.1 (K), RN1.2 (R1)
unnamed: D2.2 (A), U17.12 (B7)
unnamed: D2.1 (K), RN1.3 (R2)
unnamed: D3.2 (A), U17.13 (B6)
unnamed: D3.1 (K), RN1.4 (R3)
unnamed: D4.2 (A), U17.14 (B5)
unnamed: D4.1 (K), RN1.5 (R4)
unnamed: D5.2 (A), U17.15 (B4)
unnamed: D5.1 (K), RN1.6 (R5)
unnamed: D6.2 (A), U17.16 (B3)
unnamed: D6.1 (K), RN1.7 (R6)
unnamed: D7.2 (A), U17.17 (B2)
unnamed: D7.1 (K), RN1.8 (R7)
unnamed: D8.2 (A), U17.18 (B1)
unnamed: D8.1 (K), RN1.9 (R8)
unnamed: D9.2 (A), RN2.2 (R1)
unnamed: D9.1 (K), U18.11 (B8)
unnamed: D10.2 (A), RN2.3 (R2)
unnamed: D10.1 (K), U18.12 (B7)
unnamed: D11.2 (A), RN2.4 (R3)
unnamed: D11.1 (K), U18.13 (B6)
unnamed: D12.2 (A), RN2.5 (R4)
unnamed: D12.1 (K), U18.14 (B5)
unnamed: D13.2 (A), RN2.6 (R5)
unnamed: D13.1 (K), U18.15 (B4)
unnamed: D14.2 (A), RN2.7 (R6)
unnamed: D14.1 (K), U18.16 (B3)
unnamed: D15.2 (A), RN2.8 (R7)
unnamed: D15.1 (K), U18.17 (B2)
unnamed: D16.2 (A), RN2.9 (R8)
unnamed: D16.1 (K), U18.18 (B1)
unnamed: U19.5, U19.8
unnamed: U19.6, U19.9, U21.9
unnamed: U19.11, U21.11
unnamed: U19.3, U19.12
unnamed: U21.1, U21.2, U21.8
unnamed: C24.2, R7.2, U22.15 (RCext)
unnamed: C23.2, R6.2, U22.7 (RCext)
VCC: C1.2, C2.2, C3.2, C4.2, C5.2, C6.2, C7.2, C8.2, C9.2, C10.2, C11.2, C12.2, C13.2, C14.2, C15.2, C16.2, C17.2, C18.2, C19.2, C20.2, C21.2, C22.2, C97.1, C98.1, C99.1, J1.1 (VCC), J1.2 (VCC), J4.1, R6.1, R7.1, RN2.1 (common), RN3.1 (common), U1.20 (VCC), U2.20 (VCC), U3.20 (VCC), U4.20 (VCC), U5.20 (VCC), U6.20 (VCC), U7.20 (VCC), U8.20 (VCC), U9.20 (VCC), U10.20 (VCC), U11.20 (VCC), U12.20 (VCC), U13.20 (VCC), U14.20 (VCC), U15.16 (VCC), U16.6 (G1), U16.16 (VCC), U17.1 (DIR), U17.20 (VCC), U18.1 (DIR), U18.20 (VCC), U19.14 (VCC), U20.6 (E3), U20.16 (VCC), U21.4, U21.5, U21.14 (VCC), U22.3 (Clr), U22.11 (Clr), U22.16 (VCC)

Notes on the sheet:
Registers
OE Decode and display
Safe clock enable
Input enable decode and display

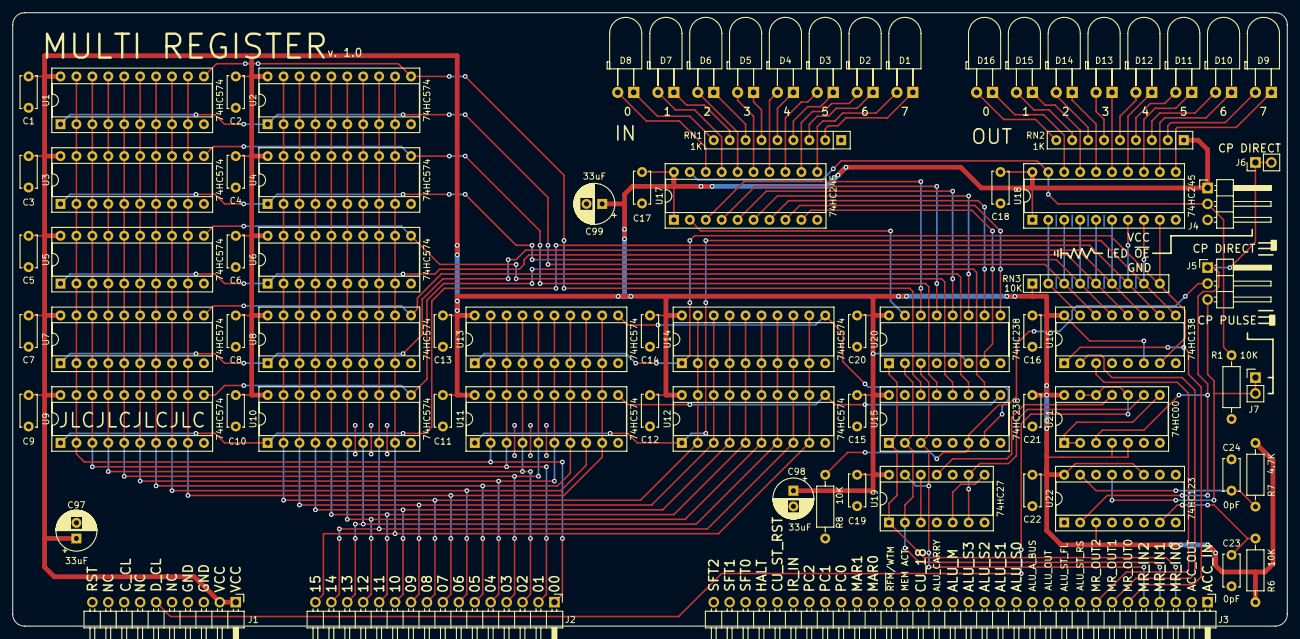
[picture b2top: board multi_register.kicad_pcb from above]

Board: 2 copper layers, 203.2 x 97.8 mm, 79 parts (0 on the bottom side), 91 nets.
